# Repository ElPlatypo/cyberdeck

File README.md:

# cyberdeck

Part List

-mainboard: Raspberry pi 5
-display: [aliexpress](https://it.aliexpress.com/item/1005005292813240.html?spm=a2g0o.order_list.order_list_main.10.1cfb3696EUqxXU&gatewayAdapt=glo2ita)
-fan: [aliexprss](https://it.aliexpress.com/item/1005006192883688.html?spm=a2g0o.productlist.main.61.6a2293d68XoCxL&algo_pvid=2c0757ac-cca5-402e-b304-105bb6a0e437&algo_exp_id=2c0757ac-cca5-402e-b304-105bb6a0e437-30&pdp_npi=4%40dis%21EUR%213.28%213.28%21%21%213.37%213.37%21%402103856417317102984366538efd54%2112000036212283153%21sea%21IT%216100837632%21X&curPageLogUid=6cfUj6alvwJD&utparam-url=scene%3Asearch%7Cquery_from%3A)
-dac for audio output: [aliexpress](https://it.aliexpress.com/item/1005007477490325.html?spm=a2g0o.order_list.order_list_main.5.3d2736964oNN51&gatewayAdapt=glo2ita)
-case: [aliexpress](https://it.aliexpress.com/item/1005006807658743.html?spm=a2g0o.order_list.order_list_main.15.1cfb3696EUqxXU&gatewayAdapt=glo2ita)

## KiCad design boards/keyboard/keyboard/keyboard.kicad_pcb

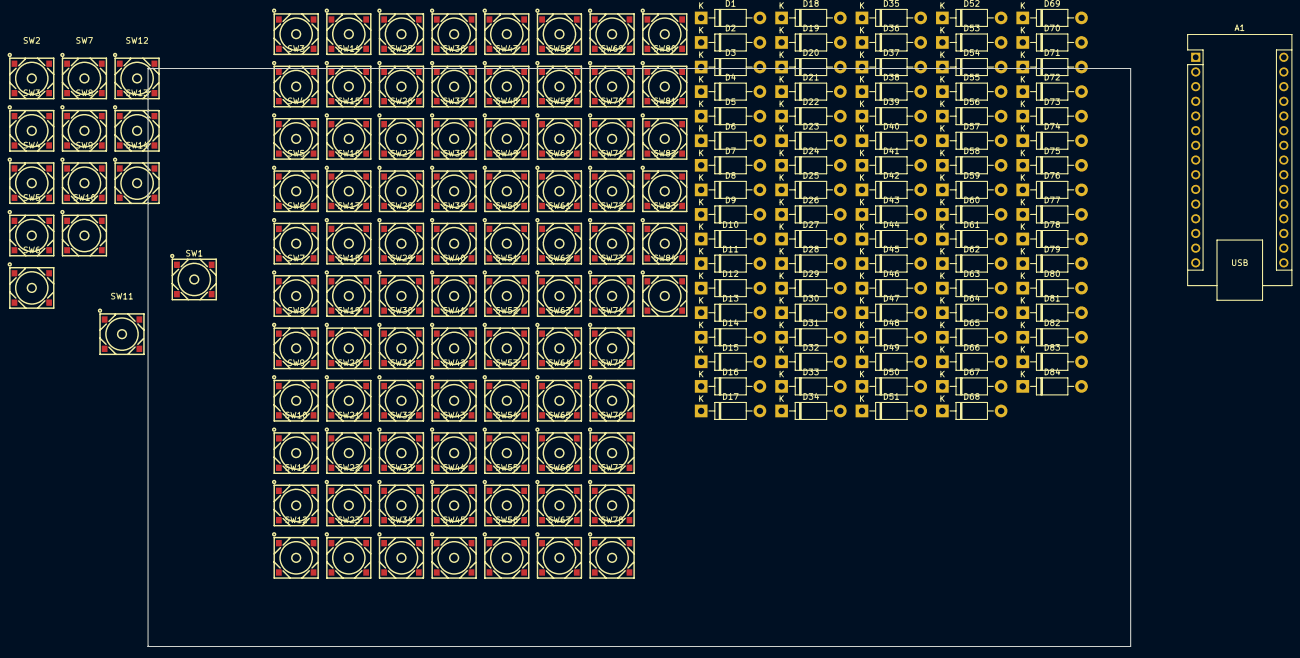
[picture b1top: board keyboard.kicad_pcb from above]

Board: 2 copper layers, 170.0 x 100.0 mm, 182 parts (0 on the bottom side), 104 nets, no tracks yet.

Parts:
A1: Arduino_Nano_v3.x; Arduino_Nano
D1, D2, D3, D4, D5, D6, D7, D8, D9, D10, D11, D12, D13, D14, D15, D16, D17, D18, D19, D20, D21, D22, D23, D24, D25, D26, D27, D28, D29, D30, D31, D32, D33, D34, D35, D36, D37, D38, D39, D40, D41, D42, D43, D44, D45, D46, D47, D48, D49, D50, D51, D52, D53, D54, D55, D56, D57, D58, D59, D60, D61, D62, D63, D64, D65, D66, D67, D68, D69, D70, D71, D72, D73, D74, D75, D76, D77, D78, D79, D80, D81, D82, D83, D84: 1N4001; D_DO-41_SOD81_P10.16mm_Horizontal
SW1, SW2, SW2#2, SW3, SW3#2, SW4, SW4#2, SW5, SW5#2, SW6, SW6#2, SW7, SW7#2, SW8, SW8#2, SW9, SW9#2, SW10, SW10#2, SW11, SW11#2, SW12, SW12#2, SW13, SW13#2, SW14, SW14#2, SW15, SW16, SW17, SW18, SW19, SW20, SW21, SW22, SW23, SW24, SW25, SW26, SW27, SW28, SW29, SW30, SW31, SW32, SW33, SW34, SW35, SW36, SW37, SW38, SW39, SW40, SW41, SW42, SW43, SW44, SW45, SW46, SW47, SW48, SW49, SW50, SW51, SW52, SW53, SW54, SW55, SW56, SW57, SW58, SW59, SW60, SW61, SW62, SW63, SW64, SW65, SW66, SW67, SW68, SW69, SW70, SW71, SW72, SW73, SW74, SW75, SW76, SW77, SW78, SW79, SW80, SW81, SW82, SW83, SW84: SKRRAAE010; KEY-SMD_4P-L7.5-W7.0-P6.00-LS5.0

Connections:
unnamed: D1.2 (A), SW1.4
unnamed: D2.2 (A), SW2#2.4
unnamed: D3.2 (A), SW3#2.4
unnamed: D4.2 (A), SW4#2.4
unnamed: D5.2 (A), SW5#2.4
unnamed: D6.2 (A), SW6.4
unnamed: D7.2 (A), SW7.4
unnamed: D8.2 (A), SW8.4
unnamed: D9.2 (A), SW9.4
unnamed: D10.2 (A), SW10.4
unnamed: D11.2 (A), SW11#2.4
unnamed: D12.2 (A), SW12#2.4
unnamed: D13.2 (A), SW13.4
unnamed: D14.2 (A), SW14.4
unnamed: D15.2 (A), SW15.4
unnamed: D16.2 (A), SW16.4
unnamed: D17.2 (A), SW17.4
unnamed: D18.2 (A), SW18.4
unnamed: D19.2 (A), SW19.4
unnamed: D20.2 (A), SW20.4
unnamed: D21.2 (A), SW21.4
unnamed: D22.2 (A), SW22.4
unnamed: D23.2 (A), SW23.4
unnamed: D24.2 (A), SW24.4
unnamed: D25.2 (A), SW25.4
unnamed: D26.2 (A), SW26.4
unnamed: D27.2 (A), SW27.4
unnamed: D28.2 (A), SW28.4
unnamed: D29.2 (A), SW29.4
unnamed: D30.2 (A), SW30.4
unnamed: D31.2 (A), SW31.4
unnamed: D32.2 (A), SW32.4
unnamed: D33.2 (A), SW33.4
unnamed: D34.2 (A), SW34.4
unnamed: D35.2 (A), SW35.4
unnamed: D36.2 (A), SW36.4
unnamed: D37.2 (A), SW37.4
unnamed: D38.2 (A), SW38.4
unnamed: D39.2 (A), SW39.4
unnamed: D40.2 (A), SW40.4
unnamed: D41.2 (A), SW41.4
unnamed: D42.2 (A), SW42.4
unnamed: D43.2 (A), SW43.4
unnamed: D44.2 (A), SW44.4
unnamed: D45.2 (A), SW45.4
unnamed: D46.2 (A), SW46.4
unnamed: D47.2 (A), SW47.4
unnamed: D48.2 (A), SW48.4
unnamed: D49.2 (A), SW49.4
unnamed: D50.2 (A), SW50.4
unnamed: D51.2 (A), SW51.4
unnamed: D52.2 (A), SW52.4
unnamed: D53.2 (A), SW53.4
unnamed: D54.2 (A), SW54.4
unnamed: D55.2 (A), SW55.4
unnamed: D56.2 (A), SW56.4
unnamed: D57.2 (A), SW57.4
unnamed: D58.2 (A), SW58.4
unnamed: D59.2 (A), SW59.4
unnamed: D60.2 (A), SW60.4
unnamed: D61.2 (A), SW61.4
unnamed: D62.2 (A), SW62.4
unnamed: D63.2 (A), SW63.4
unnamed: D64.2 (A), SW64.4
unnamed: D65.2 (A), SW65.4
unnamed: D66.2 (A), SW66.4
unnamed: D67.2 (A), SW67.4
unnamed: D68.2 (A), SW68.4
unnamed: D69.2 (A), SW69.4
unnamed: D70.2 (A), SW70.4
unnamed: D71.2 (A), SW71.4
unnamed: D72.2 (A), SW72.4
unnamed: D73.2 (A), SW73.4
unnamed: D74.2 (A), SW74.4
unnamed: D75.2 (A), SW75.4
unnamed: D76.2 (A), SW76.4
unnamed: D77.2 (A), SW77.4
unnamed: D78.2 (A), SW78.4
unnamed: D79.2 (A), SW79.4
unnamed: D80.2 (A), SW80.4
unnamed: D81.2 (A), SW81.4
unnamed: D82.2 (A), SW82.4
unnamed: D83.2 (A), SW83.4
unnamed: D84.2 (A), SW84.4
col 0: A1.11 (D8), SW1.1, SW15.1, SW29.1, SW30.1, SW57.1, SW58.1
col 1: A1.12 (D9), SW2#2.1, SW16.1, SW31.1, SW32.1, SW59.1, SW60.1
col 2: A1.13 (D10), SW3#2.1, SW17.1, SW33.1, SW34.1, SW61.1, SW62.1
col 3: A1.14 (D11), SW4#2.1, SW18.1, SW35.1, SW36.1, SW63.1, SW64.1
col 4: A1.15 (D12), SW5#2.1, SW19.1, SW37.1, SW38.1, SW65.1, SW66.1
col 5: A1.16 (D13), SW6.1, SW20.1, SW39.1, SW40.1, SW67.1, SW68.1
col 6: A1.26 (A7), SW7.1, SW21.1, SW41.1, SW42.1, SW69.1, SW70.1
col 7: A1.25 (A6), SW8.1, SW22.1, SW43.1, SW44.1, SW71.1, SW72.1
col 8: A1.24 (A5), SW9.1, SW23.1, SW45.1, SW46.1, SW73.1, SW74.1
col 9: A1.23 (A4), SW10.1, SW24.1, SW47.1, SW48.1, SW75.1, SW76.1
col 10: A1.22 (A3), SW11#2.1, SW25.1, SW49.1, SW50.1, SW77.1, SW78.1
col 11: A1.21 (A2), SW12#2.1, SW26.1, SW51.1, SW52.1, SW79.1, SW80.1
col 12: A1.20 (A1), SW13.1, SW27.1, SW53.1, SW54.1, SW81.1, SW82.1
col 13: A1.19 (A0), SW14.1, SW28.1, SW55.1, SW56.1, SW83.1, SW84.1
row 0: A1.5 (D2), D1.1 (K), D2.1 (K), D3.1 (K), D4.1 (K), D5.1 (K), D6.1 (K), D7.1 (K), D8.1 (K), D9.1 (K), D10.1 (K), D11.1 (K), D12.1 (K), D13.1 (K), D14.1 (K)
row 1: A1.6 (D3), D15.1 (K), D16.1 (K), D17.1 (K), D18.1 (K), D19.1 (K), D20.1 (K), D21.1 (K), D22.1 (K), D23.1 (K), D24.1 (K), D25.1 (K), D26.1 (K), D27.1 (K), D28.1 (K)
row 2: A1.7 (D4), D29.1 (K), D31.1 (K), D33.1 (K), D35.1 (K), D37.1 (K), D39.1 (K), D41.1 (K), D43.1 (K), D45.1 (K), D47.1 (K), D49.1 (K), D51.1 (K), D53.1 (K), D55.1 (K)
row 3: A1.8 (D5), D30.1 (K), D32.1 (K), D34.1 (K), D36.1 (K), D38.1 (K), D40.1 (K), D42.1 (K), D44.1 (K), D46.1 (K), D48.1 (K), D50.1 (K), D52.1 (K), D54.1 (K), D56.1 (K)
row 4: A1.9 (D6), D57.1 (K), D59.1 (K), D61.1 (K), D63.1 (K), D65.1 (K), D67.1 (K), D69.1 (K), D71.1 (K), D73.1 (K), D75.1 (K), D77.1 (K), D79.1 (K), D81.1 (K), D83.1 (K)
row 5: A1.10 (D7), D58.1 (K), D60.1 (K), D62.1 (K), D64.1 (K), D66.1 (K), D68.1 (K), D70.1 (K), D72.1 (K), D74.1 (K), D76.1 (K), D78.1 (K), D80.1 (K), D82.1 (K), D84.1 (K)

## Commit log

2024-11-02 added image
2024-11-03 reworked bottom frame to make it lower profile
2024-11-03 more work
2024-11-04 reworked top helf and added air ducts
2024-11-04 restructured item groups
2024-11-15 reworked top airlow, updated readme
2024-11-15 fixed readme
2024-11-27 changed Fan to 5v model, added slot for DAC
2024-11-27 updated image
2025-02-01 reworked frame, started kikad proj
